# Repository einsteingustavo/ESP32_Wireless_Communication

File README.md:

# ESP32_Wireless_Communication
This project aims to make it possible to send a 500Kb file over a distance of 100m, through a completely wireless system. For these purposes, an ESP32 microcontroller, an LM2596 switching power supply and an nRF24L01 radio frequency module were chosen (The choices were made through decision matrices available in this repository). The software is generic, so it is only necessary to modify a "#define" at the beginning of the code to switch between transmitter and receiver. After loading the software, the system works as follows: Each PCB is powered by a 12~24V battery at a distance of 100m from each other. For the file to be available on the transmitter, just connect your smartphone or laptop via bluetooth and send the file, as soon as the ESP32 recognizes that a file has arrived, it sends it via radio to the receiver, which will update the data whenever there is a new reception, and if any device is connected, the receiver sends the file via bluetooth. This project does not include an Android application specifically for sending files, although the idea is to always send the file as a string, with the first byte always referring to the file format, so that a proper conversion can happen on the other side.

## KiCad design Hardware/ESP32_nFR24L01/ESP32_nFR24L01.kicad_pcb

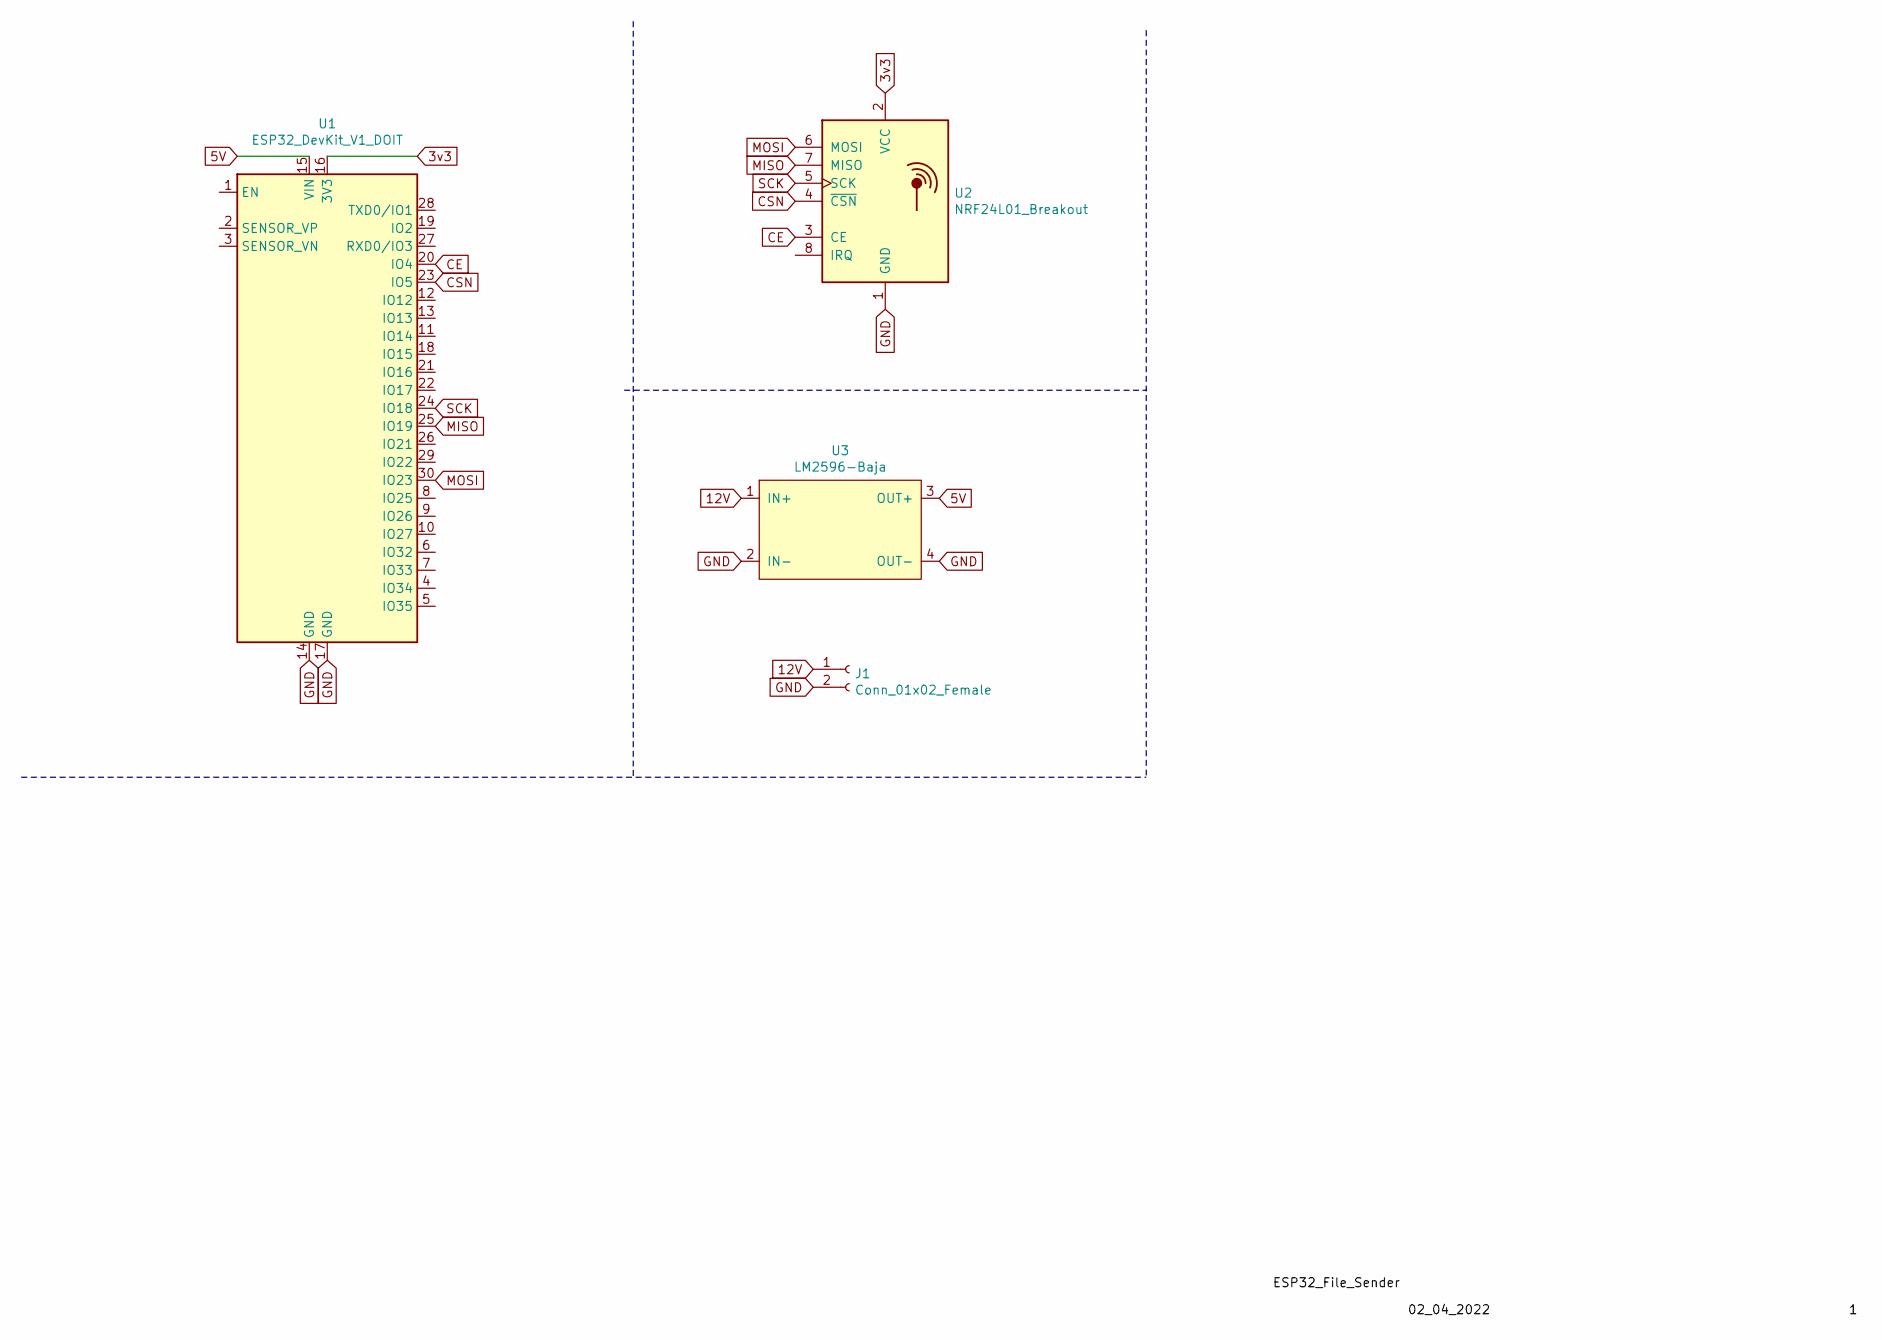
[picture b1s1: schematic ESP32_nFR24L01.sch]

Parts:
J1: Conn_01x02_Female; JST_EH_S2B-EH_1x02_P2.50mm_Horizontal
U1: ESP32_DevKit_V1_DOIT; esp32_devkit_v1_doit
U2: NRF24L01_Breakout; NRF24L01Module
U3: LM2596-Baja; LM2596

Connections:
3v3: U1.16 (3V3), U2.2 (VCC)
5V: U1.15 (VIN), U3.3 (OUT+)
12V: J1.1, U3.1 (IN+)
CE: U1.20 (IO4), U2.3 (CE)
CSN: U1.23 (IO5), U2.4 (~CSN)
GND: J1.2, U1.14 (GND), U1.17 (GND), U2.1 (GND), U3.2 (IN-), U3.4 (OUT-)
MISO: U1.25 (IO19), U2.7 (MISO)
MOSI: U1.30 (IO23), U2.6 (MOSI)
SCK: U1.24 (IO18), U2.5 (SCK)

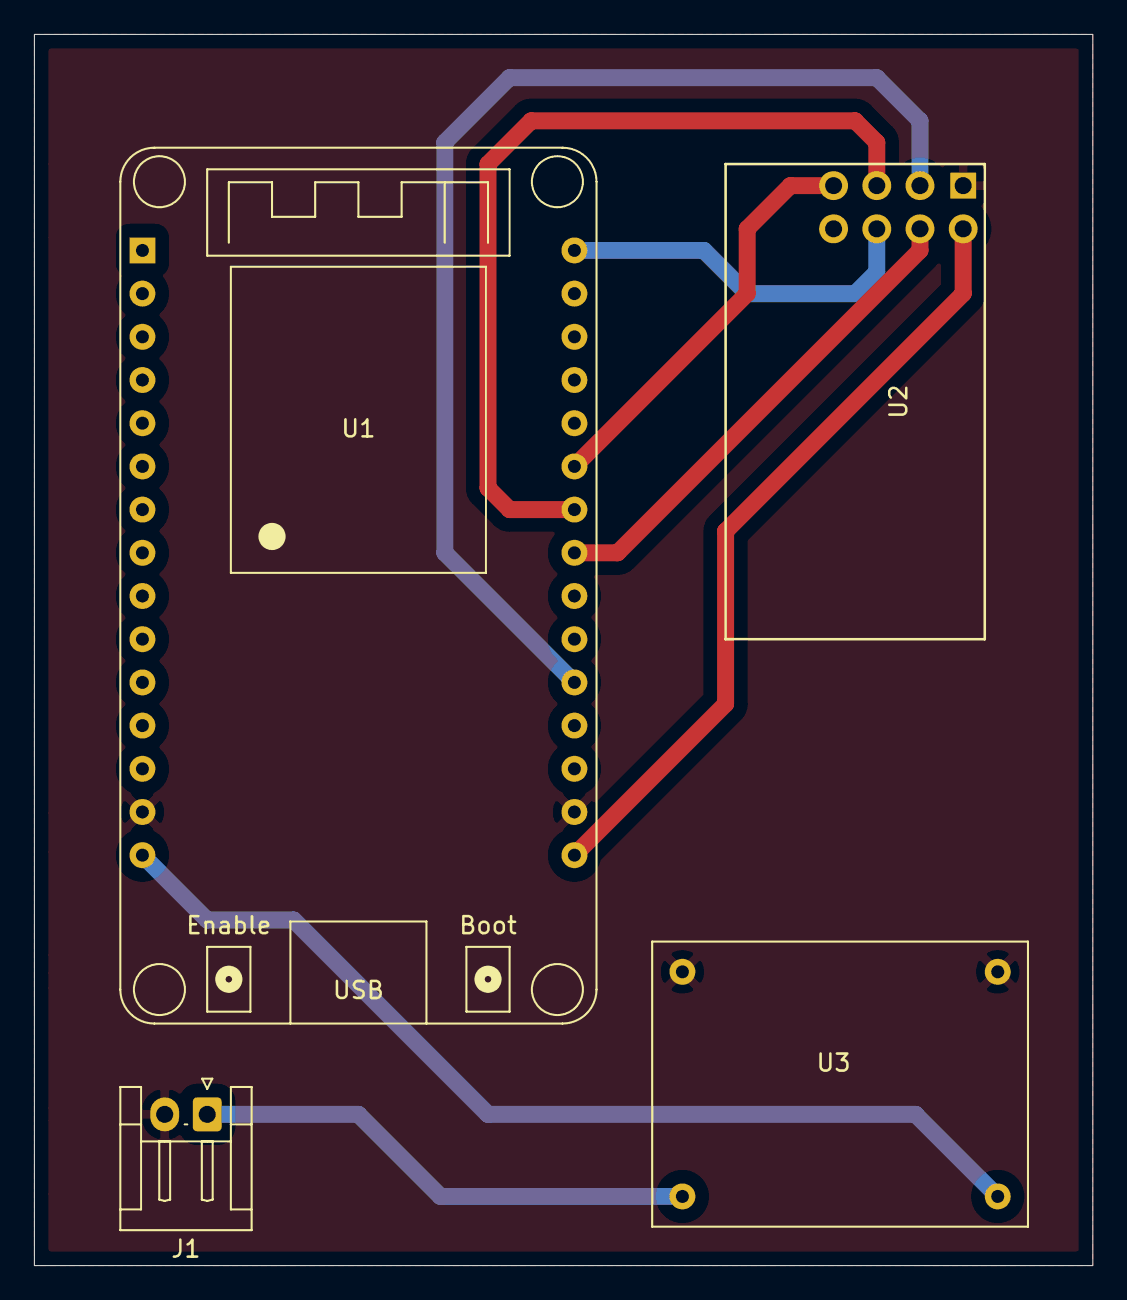
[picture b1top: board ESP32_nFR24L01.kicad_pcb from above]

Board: 2 copper layers, 62.2 x 72.4 mm, 4 parts (0 on the bottom side), 9 nets.

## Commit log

2022-04-04 First commit, next step is validation.
2022-04-04 Fix LISTENER code
2022-04-04 Add PCB outline
2022-04-04 Add a simple costs table
